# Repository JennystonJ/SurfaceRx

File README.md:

# SurfaceRx
An ARM based surface vehicle receiver

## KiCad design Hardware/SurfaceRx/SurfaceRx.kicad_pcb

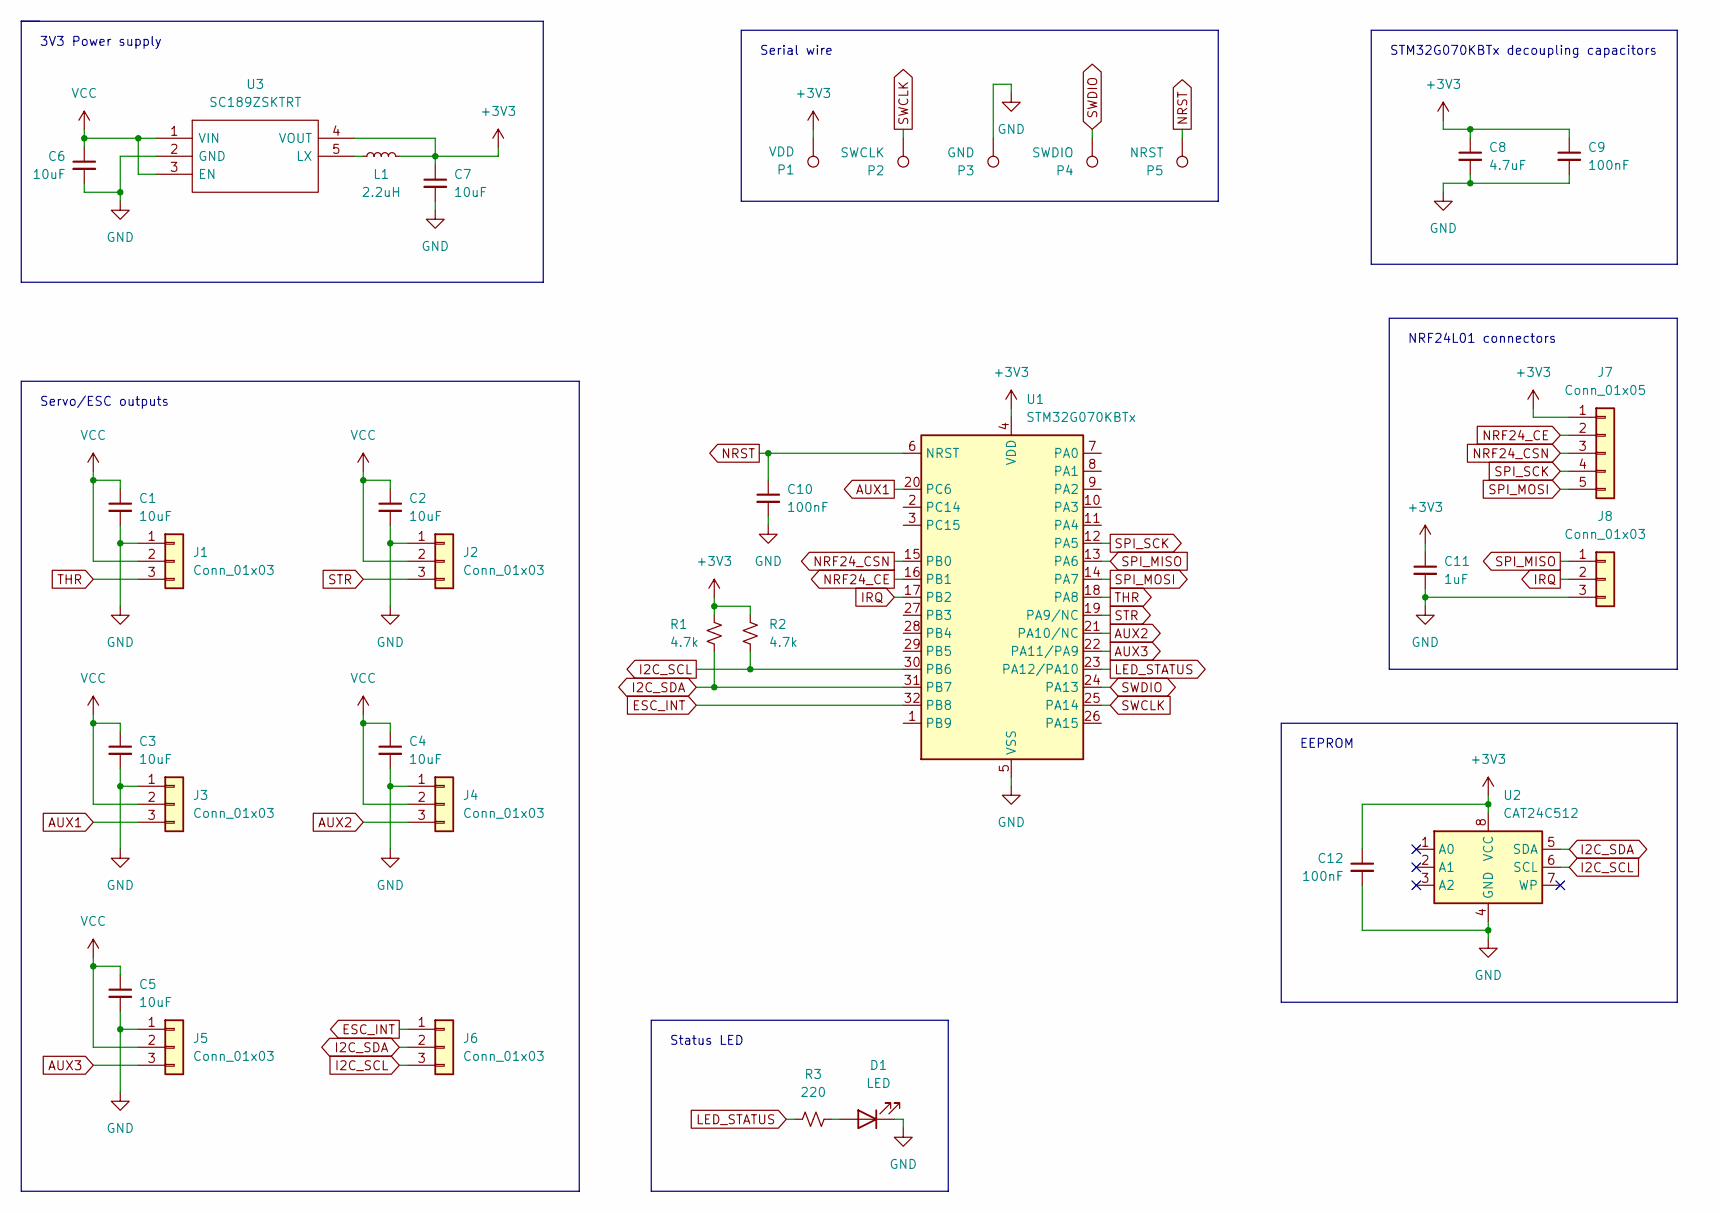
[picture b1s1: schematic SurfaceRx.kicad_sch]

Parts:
C1, C2, C3, C4, C5, C6, C7: 10uF; C_0603_1608Metric
C8: 4.7uF; C_0603_1608Metric
C9, C10, C12: 100nF; C_0603_1608Metric
C11: 1uF; C_0603_1608Metric
D1: LED; LED_0603_1608Metric
J1, J2, J3, J4, J5, J8: Conn_01x03; PinHeader_1x03_P2.54mm_Vertical
J6: Conn_01x03; JST-SH_3_Top
J7: Conn_01x05; PinHeader_1x05_P2.54mm_Vertical
L1: 2.2uH; L-3.0x3.0mm; Part # VLS3015CX-2R2M-H
P1: VDD; TestPoint_Pad_D1.5mm
P2: SWCLK; TestPoint_Pad_D1.5mm
P3: GND; TestPoint_Pad_D1.5mm
P4: SWDIO; TestPoint_Pad_D1.5mm
P5: NRST; TestPoint_Pad_D1.5mm
R1, R2: 4.7k; R_0603_1608Metric
R3: 220; R_0603_1608Metric
U1: STM32G070KBTx; LQFP-32_7x7mm_P0.8mm
U2: CAT24C512; TSSOP-8_4.4x3mm_P0.65mm
U3: SC189ZSKTRT; SOT95P280X145-5N; Mouser Part Number 947-SC189ZSKTRT

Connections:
+3V3: C7.1, C8.1, C9.1, C11.1, C12.1, J7.1, L1.2, P1.1, R1.1, R2.1, U1.4 (VDD), U2.8 (VCC), U3.4 (VOUT)
AUX1: J3.3, U1.20 (PC6)
AUX2: J4.3, U1.21 (PA10/NC)
AUX3: J5.3, U1.22 (PA11/PA9)
ESC_INT: J6.1, U1.32 (PB8)
GND: C1.2, C2.2, C3.2, C4.2, C5.2, C6.2, C7.2, C8.2, C9.2, C10.2, C11.2, C12.2, D1.1 (K), J1.1, J2.1, J3.1, J4.1, J5.1, J8.3, P3.1, U1.5 (VSS), U2.4 (GND), U3.2 (GND)
I2C_SCL: J6.3, R2.2, U1.30 (PB6), U2.6 (SCL)
I2C_SDA: J6.2, R1.2, U1.31 (PB7), U2.5 (SDA)
IRQ: J8.2, U1.17 (PB2)
LED_STATUS: R3.2, U1.23 (PA12/PA10)
NRF24_CE: J7.2, U1.16 (PB1)
NRF24_CSN: J7.3, U1.15 (PB0)
NRST: C10.1, P5.1, U1.6 (NRST)
unnamed: D1.2 (A), R3.1
unnamed: L1.1, U3.5 (LX)
SPI_MISO: J8.1, U1.13 (PA6)
SPI_MOSI: J7.5, U1.14 (PA7)
SPI_SCK: J7.4, U1.12 (PA5)
STR: J2.3, U1.19 (PA9/NC)
SWCLK: P2.1, U1.25 (PA14)
SWDIO: P4.1, U1.24 (PA13)
THR: J1.3, U1.18 (PA8)
VCC: C1.1, C2.1, C3.1, C4.1, C5.1, C6.1, J1.2, J2.2, J3.2, J4.2, J5.2, U3.1 (VIN), U3.3 (EN)

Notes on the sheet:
STM32G070KBTx decoupling capacitors
Status LED
Servo/ESC outputs
EEPROM
3V3 Power supply
Serial wire
NRF24L01 connectors

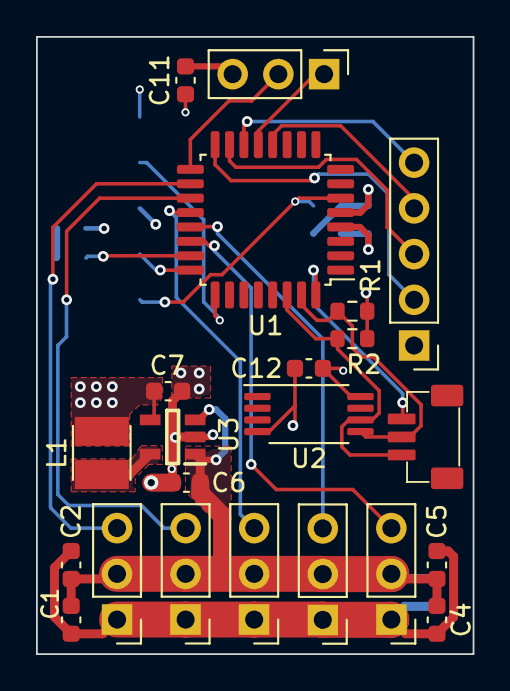
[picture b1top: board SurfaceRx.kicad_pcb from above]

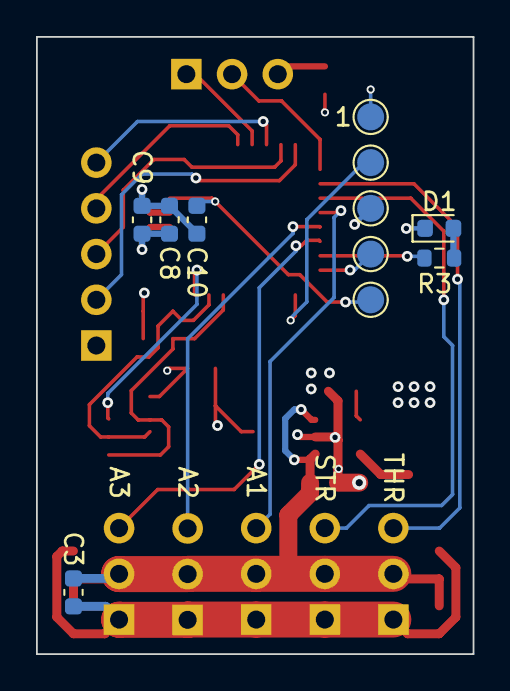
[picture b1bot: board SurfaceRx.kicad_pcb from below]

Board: 4 copper layers, 24.3 x 34.3 mm, 33 parts (11 on the bottom side), 23 nets.

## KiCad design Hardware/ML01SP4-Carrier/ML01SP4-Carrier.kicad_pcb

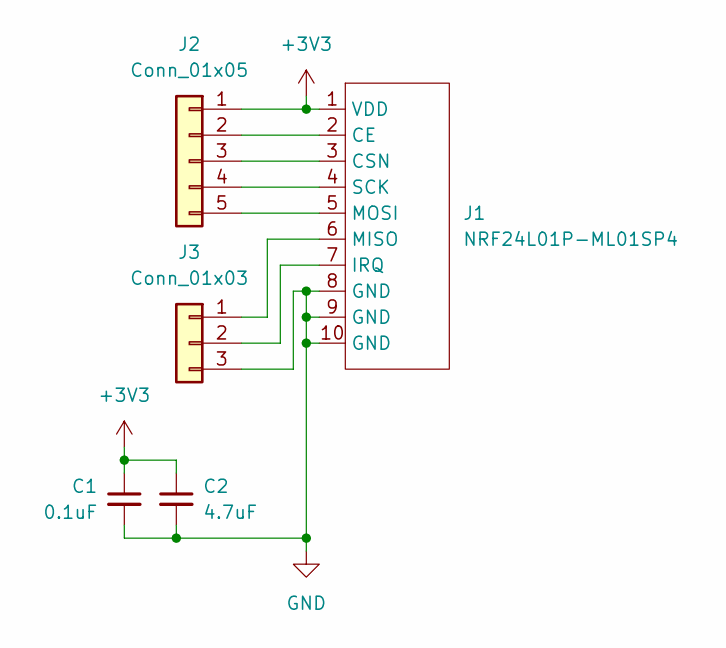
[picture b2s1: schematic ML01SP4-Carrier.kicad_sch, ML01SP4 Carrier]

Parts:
C1: 0.1uF; C_0603_1608Metric
C2: 4.7uF
J1: NRF24L01P-ML01SP4; ML01SP4
J2: Conn_01x05; PinHeader_1x05_P2.54mm_Vertical
J3: Conn_01x03; PinHeader_1x03_P2.54mm_Vertical

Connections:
+3V3: C1.1, C2.1, J1.1 (VDD), J2.1
GND: C1.2, C2.2, J1.8 (GND), J1.9 (GND), J1.10 (GND), J3.3
unnamed: J1.2 (CE), J2.2
unnamed: J1.3 (CSN), J2.3
unnamed: J1.4 (SCK), J2.4
unnamed: J1.5 (MOSI), J2.5
unnamed: J1.6 (MISO), J3.1
unnamed: J1.7 (IRQ), J3.2

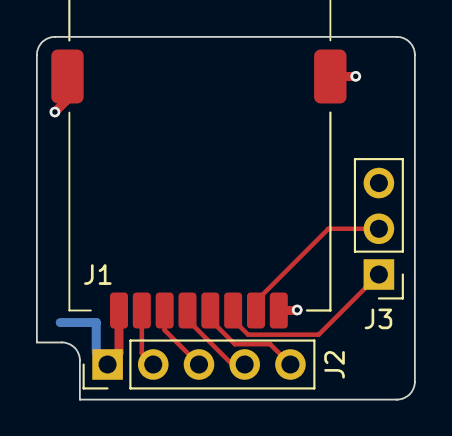
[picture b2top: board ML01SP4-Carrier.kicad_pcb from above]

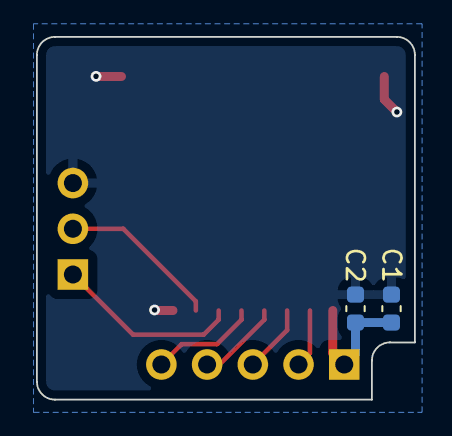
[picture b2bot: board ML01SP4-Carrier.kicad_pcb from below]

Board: 2 copper layers, 21.0 x 20.1 mm, 5 parts (2 on the bottom side), 8 nets.

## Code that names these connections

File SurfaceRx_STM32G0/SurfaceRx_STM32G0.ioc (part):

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Mcu.Name=STM32G070KBTx
Mcu.Package=LQFP32
Mcu.UserName=STM32G070KBTx
PA10.Signal=S_TIM1_CH3
PA11\ [PA9].Signal=S_TIM1_CH4
PA12\ [PA10].GPIOParameters=GPIO_Label
PA12\ [PA10].GPIO_Label=LED_STATUS
PA12\ [PA10].Signal=GPIO_Output
PA13.Mode=Serial_Wire
PA13.Signal=SYS_SWDIO
PA14-BOOT0.Mode=Serial_Wire
PA14-BOOT0.Signal=SYS_SWCLK
PA5.Mode=Full_Duplex_Master
PA5.Signal=SPI1_SCK
PA6.Mode=Full_Duplex_Master
PA6.Signal=SPI1_MISO
PA7.Mode=Full_Duplex_Master
PA7.Signal=SPI1_MOSI
PA8.Signal=S_TIM1_CH1
PA9.Signal=S_TIM1_CH2
PB0.GPIOParameters=GPIO_Label
PB0.GPIO_Label=NRF24_NCS
PB0.Signal=GPIO_Output
PB1.GPIOParameters=GPIO_Label
PB1.GPIO_Label=NRF24_CE
PB1.Signal=GPIO_Output
PB2.GPIOParameters=GPIO_Label
PB2.GPIO_Label=NRF24_INT
PB2.Signal=GPXTI2
PB6.Mode=I2C
PB6.Signal=I2C1_SCL
PB7.Mode=I2C
PB7.Signal=I2C1_SDA
PB8.GPIOParameters=GPIO_Label
PB8.GPIO_Label=ESC_INT
PB8.Signal=GPXTI8
PC6.Signal=S_TIM3_CH1
RCC.HSE_VALUE=8000000
RCC.SYSCLKFreq_VALUE=16000000
board=custom

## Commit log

2022-12-15 project rename
2022-12-20 project name changed
2023-01-06 moved nrf24 commands to own file and converted to enum
2023-01-07 initial schematic/PCB design commit
2023-01-08 added local symbol and footprint for NRF24L01
2023-01-12 created library for nrf24l01 symbol and footprint
2023-01-12 modified schematic and pcb
2023-01-12 added decoupling capacitors and rounded pcb corners
2023-01-19 changed microcontroller to STM32G070KBT
2023-01-19 created project and assigned pins
2023-01-19 created 3 pin JST-SH vertical footprint
2023-01-19 added SWD and ESC (I2C) connectors. Connected NRF24 pins
2023-01-19 annotated schematic
2023-01-26 Generated HAL code
2023-01-26 PCB partially layed out
2023-01-26 Added EEPROM symbol
2023-01-26 Added EEPROM to schematic
2023-01-26 Modified labels for clarity
2023-01-26 Replaced debug pads with single header
2023-01-27 Added status LED output
2023-01-27 Reverted debug header to pads. Added status LED
2023-01-29 Regenerated CubeMX code. Added devices, utilities, and peripherals libraries
2023-01-29 Added link to original code source
2023-01-29 Updated project files
2023-01-29 Modified PCB layout
2023-02-06 Corrected net name for SWD 3V3 pin
2023-02-06 Added ground plane, some traces routed
2023-02-09 Routed all traces
2023-02-09 Hid reference designators from silkscreen. Added silkscreen labels for servo and ESC outputs.
2023-02-09 Added reference designators on PCB for SMD components only. Changed designator from 'IC1' to 'U3'.
2023-02-11 ML01SP4-Carrier edge cuts vectors
2023-02-11 Moved to Vectors directory
2023-02-11 Layout modified, notch on edge cuts layer added.
2023-08-29 Exported paste layer.
2023-08-29 Regenerated CubeMx code. Rearranged radio packet and added radio config.
2023-08-29 Regenerated CubeMX code.
